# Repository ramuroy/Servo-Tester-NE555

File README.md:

# ⚙️ Servo Tester using NE555 Timer

## 📌 Overview  
This is a **PCB design** for a **servo motor tester**, created using **KiCad**. The circuit is based on the **NE555 timer IC** in **astable mode**, generating PWM signals to control servo motor position. It's a simple tool useful for testing and calibrating servo motors without a microcontroller.

## 🛠️ Specifications  
- **Input Voltage**: 6V DC  
- **Timer IC**: NE555P  
- **PWM Output**: Variable duty cycle based on RC network  
- **Output**: 3-pin servo header (VCC, GND, Signal)

## 🧾 Bill of Materials
| Component | Value / Part | Qty |
|-----------|--------------|:---:|
| Timer IC | NE555P | 1 |
| Timing diode | 1N4148 | 1 |
| Timing capacitor | 22 nF | 1 |
| Resistor | 56 kΩ | 1 |
| Potentiometer (pulse-width adjust) | — | 1 |
| Power-indicator LED + resistor | — | 1 + 1 |
| Servo header | 3-pin (VCC/GND/Signal) | 1 |

> Key components from the design specifications; see the schematic for exact values of any remaining passives.

## 📂 What's in this repo
- **`Schematics/`** — KiCad schematic source (`Servo Tester.kicad_sch`) + exported PNG
- **`PCB_Design/`** — KiCad PCB source (`Servo Tester.kicad_pcb`) + exported PNG
- **`Gerber_Files/`** — ready-to-manufacture Gerbers (`Gerber files.zip`)
- **`Images/`** — schematic, layout, and 3D renders

## 🖼️ Preview Images  
| Schematic | PCB Layout | 3D Render |
|-----------|------------|-----------|
|  |  |  |

## 🔧 How to Use  
1️⃣ **Open the KiCad files** in `Schematics/` and `PCB_Design/` to review or customize the design.  
2️⃣ **Order the board** by sending `Gerber_Files/Gerber files.zip` to a PCB manufacturer (or regenerate Gerbers from the KiCad files).  
3️⃣ **Adjust the potentiometer** to vary the PWM signal.  
4️⃣ **Connect a servo** to the 3-pin header and power the circuit with 6V DC.

## 🙏 Credits  
This project was created with guidance from the **[Ampnics YouTube Channel](https://www.youtube.com/@ampnics)**. Thanks to their valuable tutorials!

## 🔗 Links  
- 🚀 **Project Discussion on LinkedIn**: [LinkedIn](https://www.linkedin.com/posts/ramu-roy-b780382b7_servotester-pcbdesign-ne555-activity-7327220204059430912-TQCX?utm_source=social_share_send&utm_medium=android_app&rcm=ACoAAEwAX4wBY70YZ3l58lvkiXtyCZcnWWrfJAA&utm_campaign=copy_link)  
- 📺 **Ampnics Tutorial Playlist**: [YouTube](https://youtube.com/playlist?list=PLxgq6Jtu7shQPHqYjKUVa28CmktTzHDLp&si=jp1xYo7E0JcdnXuT)

## 📜 License  
This project is licensed under the **MIT License** – feel free to use, share, and modify it!

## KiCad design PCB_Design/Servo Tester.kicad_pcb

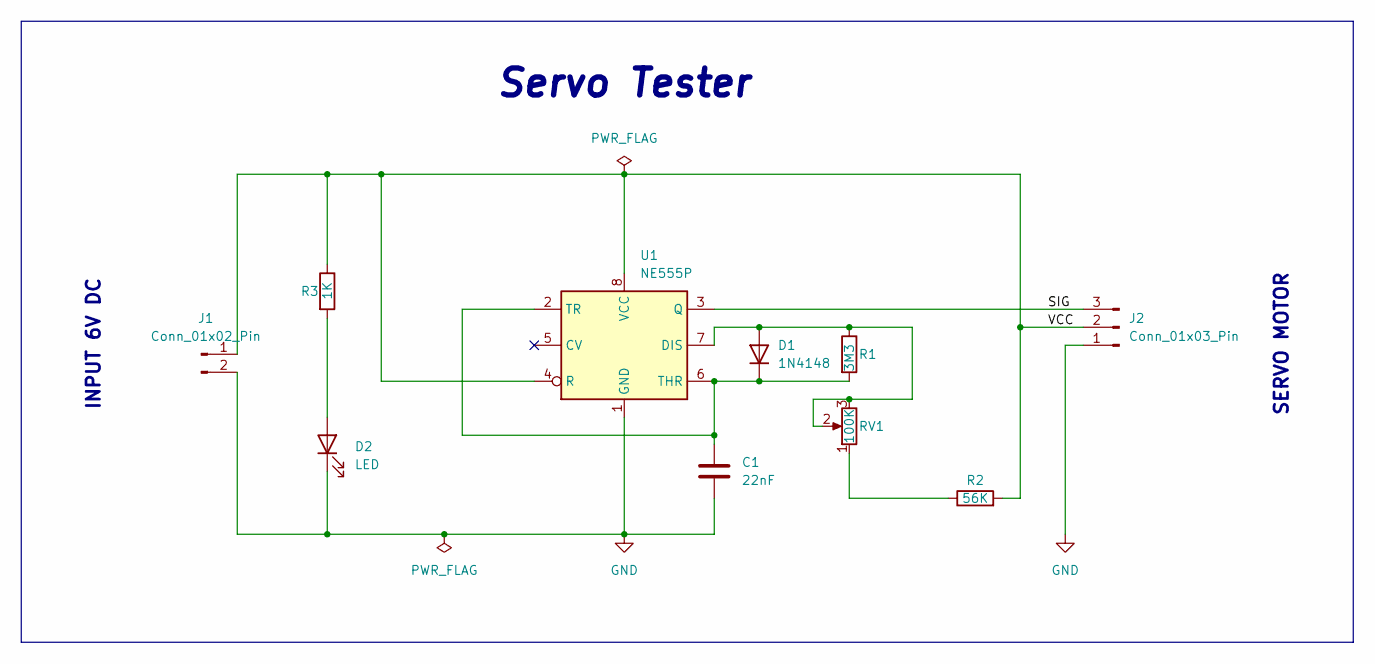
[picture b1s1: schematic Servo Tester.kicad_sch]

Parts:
C1: 22nF; C_Disc_D4.3mm_W1.9mm_P5.00mm
D1: 1N4148; D_DO-35_SOD27_P7.62mm_Horizontal
D2: LED; LED_D3.0mm
J1: Conn_01x02_Pin; PinHeader_1x02_P2.54mm_Horizontal
J2: Conn_01x03_Pin; PinHeader_1x03_P2.54mm_Horizontal
R1: 3M3; R_Axial_DIN0204_L3.6mm_D1.6mm_P7.62mm_Horizontal
R2: 56K; R_Axial_DIN0204_L3.6mm_D1.6mm_P7.62mm_Horizontal
R3: 1K; R_Axial_DIN0204_L3.6mm_D1.6mm_P7.62mm_Horizontal
RV1: 100K; Potentiometer_Alps_RK163_Single_Horizontal
U1: NE555P; DIP-8_W7.62mm

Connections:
/SIG: J2.3, U1.3 (Q)
/VCC: J1.1, J2.2, R2.2, R3.1, U1.4 (R), U1.8 (VCC)
GND: C1.2, D2.1 (K), J1.2, J2.1, U1.1 (GND)
unnamed: D1.2 (A), R1.1, RV1.2, RV1.3, U1.7 (DIS)
unnamed: C1.1, D1.1 (K), R1.2, U1.2 (TR), U1.6 (THR)
unnamed: D2.2 (A), R3.2
unnamed: R2.1, RV1.1

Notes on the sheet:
Servo Tester
INPUT 6V DC
SERVO MOTOR

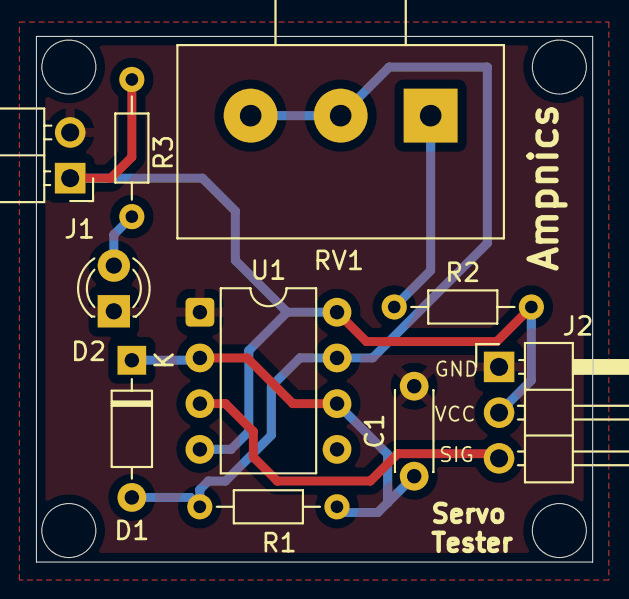
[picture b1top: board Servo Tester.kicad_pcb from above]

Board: 2 copper layers, 30.9 x 29.2 mm, 10 parts (0 on the bottom side), 7 nets.

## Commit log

2025-05-11 Rename Screenshot (76).png to Schematic.png
2025-05-11 Rename Screenshot (77).png to PCB_Layout.png
2025-05-11 Rename Screenshot (78).png to 3d_render-Top view.png
2025-05-11 Rename Screenshot (79).png to 3d_render3.png
2025-05-11 Rename Screenshot (80).png to 3d_render2.png
2025-05-11 Rename Screenshot (81).png to 3d_render1.png
2025-05-11 Rename Screenshot (82).png to Gerberfile_preview.png
2025-05-12 Update README.md
    Information about my PCB design of Servo Tester.
2026-06-27 docs: add a Bill of Materials and note the KiCad sources are included
2026-06-27 chore: remove empty placeholder files
